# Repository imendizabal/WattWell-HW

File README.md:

# Aim of the project

The main goal of the project is to develop an open source inverter (Hardware and Software).  
This inverter should exist in different configurations: Monophasic (1-ph) and threephasic (3-ph). However, it is planned to be able to add a DC/DC converter for solar applications for example.

An important part of the project is to be able to work with different types of switching components (IGBT/MOSFET). Nowadays, we often see that inverters are replaced after 10 years but they keep working or some faulty inverters that are not easily repared because the design is not modular or easy to fix.

Then, the goal is to design an Open Source inverter that is modular to be easy to be fixed and flexible enough to have differents functionalities (batteries/PV/...)

The project will be divided into different "workpackages" or sub projects, on Hardware side we have:

1. Control board: development of the main control board able to get the measurements, generate PWM's, ... This board embeds the main mcu.
2. Driver board: interface between the control board and power switch (IGBT's/Mosfet's)
3. Power circuit: power circuit of the inverter (LCL filter, DC bus, ...)

on the firmware side (main mcu based on STM32G434):

1. Low level drivers
2. Basics functionalities (bootloader, debug uart, pll,...)
3. Advanced functionalities (power management, MPPT, state machine)

# Expected functionalities

- Being able (and allowed) to be connected to the European grid
- MPPT for solar panels (with DC/DC)
- Battery connection
- Communication capabilities (serial,...)
- Working in islanding mode (offgrid)

# 1. main control board:

The main control board will be able to measure:
1.  3AC voltages (max 400V) - ADC min 14bits
2.  2DC voltages (max 1500V) -ADC min 14bits
3.  4AC/DC current measurement - ADC min 14bits
4.  Temperature measurement

The main control board will have the following interface:
1.  2X UART(1X to RS485; 1X to USB)
2.  1xSPI
3.  2xI2C
4.  1xCAN
5.  6X PWM's
6.  6X DO's
7.  6X DI's
8.  6X AI'S (temp from IGBT/Mos)

Other functions:
1.  Debug LED
2.  RTC (supercap based)
3.  Additionnal ROM (TBD)
4.  Watchdog
5.  Power supply for IGBT's/Mosfets

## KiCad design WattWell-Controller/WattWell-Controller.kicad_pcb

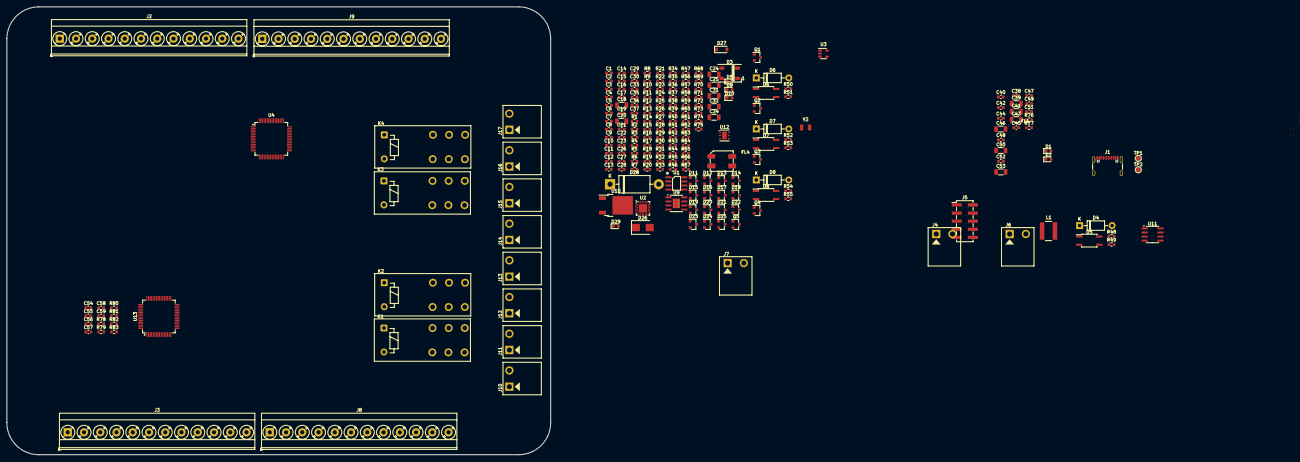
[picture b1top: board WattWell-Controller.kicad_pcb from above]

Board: 2 copper layers, 170.0 x 140.0 mm, 218 parts (0 on the bottom side), 168 nets, no tracks yet.

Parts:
C1, C3, C5, C7, C8, C10, C11, C12, C13, C14, C21, C22, C23, C27, C30, C33, C35, C36, C37, C49, C52: 100nF; C_0603_1608Metric
C2, C4, C6, C17, C19, C38, C40, C42, C44, C45, C47, C48, C51: 1uF; C_0603_1608Metric
C9: 10nF; C_0603_1608Metric
C15, C16: 9pF; C_0603_1608Metric
C18, C20, C39, C41, C43, C46, C50, C53: 22uF; C_1206_3216Metric
C24, C25: 10uF; C_1206_3216Metric
C26: 22nF; C_0603_1608Metric
C28: 47pF; C_0603_1608Metric
C29: 4.7nF; C_0603_1608Metric
C31, C32, C34: 47uF; C_1206_3216Metric
C54, C55, C56, C57, C58, C59: 1nF; C_0603_1608Metric
D1, D2: LED_Small; LED_0603_1608Metric
D3: WS2812B; LED_WS2812B_PLCC4_5.0x5.0mm_P3.2mm
D4, D6, D7, D8: 1N47xxA; D_DO-41_SOD81_P10.16mm_Horizontal
D5, D9, D10, D29: 150060RS55040; LED_0603_1608Metric
D11, D25: TVS_2-Channel-7V; SOT-23
D12: 824022; SOT-23
D13, D14, D15, D16, D17, D18, D19, D20, D21, D22, D23, D24: PESD3V3L2BT; SOT-23
D26: SMBJ30CA; D_SMB
D27: Zener_6V; D_SOD-123
D28: 1N5820; D_DO-201AD_P15.24mm_Horizontal
FL1, FL2, FL3: TCM0403M-350-2P-T210; Choke_TDK_TCM0403M-350-2P-T210
FL4: ACM7060-701-2PL-TL01; ChokeSMD_ACM7060
J1: USB_C_Receptacle_USB2.0; USB_C_Receptacle_GCT_USB4105-xx-A_16P_TopMnt_Horizontal
J2, J3, J8, J9: TerminalBlock_1x12; TerminalBlock_Phoenix_MKDS-3-12-5.08_1x12_P5.08mm_Horizontal
J4, J6, J7, J10, J11, J12, J13, J14, J15, J16, J17: 1x02; WURTH-691312510002
J5: Conn_ARM_JTAG_SWD_10; PinHeader_2x05_P2.54mm_Vertical_SMD
K1, K2, K3, K4: RZH3-1C4-D012; Relay_TE_RZH3-1C04-D012
L1: 10μH-5A; Inductor_Wurth_XHMI-6060
Q1, Q2, Q3, Q4: MMSS8050-H-TP; SOT-23
Q5: SI2347DS-T1-GE3; SOT-23
R1, R48, R49, R50, R51, R52, R53, R54, R55, R72, R73, R74: 120Ω; R_0603_1608Metric
R2, R3, R45, R46: 0; R_0603_1608Metric
R4, R5, R14, R15, R16, R17, R18, R19, R20, R21, R22, R23, R26, R27, R28, R29, R30, R31, R32, R33, R34, R35, R36, R37, R38, R39, R40, R41, R42, R47, R56, R57, R58, R59, R60, R61, R62, R63, R64, R65, R66, R67: 100; R_0603_1608Metric
R6: 22K1; R_0603_1608Metric
R7: 47K5; R_0603_1608Metric
R8, R78, R79, R80, R81, R82, R83: 1K; R_0603_1608Metric
R9, R10: 470Ω; R_0603_1608Metric
R11, R13, R43, R44, R76, R77: 10KΩ; R_0603_1608Metric
R12, R24, R25: 4K7; R_0603_1608Metric
R68: 12K; R_0603_1608Metric
R69: 49.9; R_0603_1608Metric
R70: 43KΩ; R_0603_1608Metric
R71: 8.2KΩ; R_0603_1608Metric
R75: 330; R_0603_1608Metric
TP1, TP2: TestPoint_1.5mm; TestPoint_Pad_D1.5mm
U1: SP3485EN; SOIC-8_3.9x4.9mm_P1.27mm
U2: CP2102N-A02-GQFN24; QFN-24-1EP_4x4mm_P0.5mm_EP2.6x2.6mm
U3: STWD100; SOT-23-5
U4, U13: LQFP-64_10x10mm_P0.5mm
U5, U6, U7, U8: LTV-356T; SO-4_4.4x3.6mm_P2.54mm
U9: TPS54331DR; SOIC-8-1EP_3.9x4.9mm_P1.27mm_EP2.29x3mm_ThermalVias
U10: BD33FC0FP-E2; TO-252-2
U11: ATA6560; SOIC-8_3.9x4.9mm_P1.27mm
U12: HDC2080; Texas_PWSON-N6
Y2: Crystal; Oscillator_SMD_ECS_2520MV-xxx-xx-4Pin_2.5x2.0mm

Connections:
+3V3: C1.1, C2.1, C8.1, C11.1, C12.1, C13.1, C14.1, C21.1, C22.1, C23.1, C34.1, C35.1, C36.1, C44.1, C46.1, C48.1, C50.1, D1.2 (K), D2.2 (K), J5.1 (VTref), R2.1, R8.1, R13.2, R24.2, R25.1, R45.1, R74.1, U2.5 (VIO), U2.6 (VDD), U2.7 (VREGIN), U3.5 (VCC), U4.16 (VDD), U4.29 (VDDA), U4.32 (VDD), U4.48 (VDD), U4.64 (VDD), U10.3 (Vout), U11.3 (VCC), U12.5 (VDD)
+5V: C17.1, C18.1, C19.1, C20.1, C31.1, C32.1, C33.1, C37.1, C38.1, C39.1, C40.1, C41.1, C42.1, C43.1, D3.4 (VDD), L1.2, R3.1, R70.1, R75.1, U10.1 (Vin)
+BATT: C10.1, U4.1 (VBAT)
/CAN_N: FL3.4, U11.6 (CANL)
/CAN_P: FL3.2, U11.7 (CANH)
/Dry Contact_1/DRY1_C: J11.2, K1.12
/Dry Contact_1/DRY1_O: J11.1, K1.14
/Dry Contact_1/DRY_CONT: J10.2, K1.11
/Dry Contact_1/DRY_V: D4.1 (K), J10.1, K1.A2, U5.4
/Dry Contact_2/DRY1_C: J12.2, K2.12
/Dry Contact_2/DRY1_O: J12.1, K2.14
/Dry Contact_2/DRY_CONT: J13.2, K2.11
/Dry Contact_2/DRY_V: D6.1 (K), J13.1, K2.A2, U6.4
/Dry Contact_3/DRY1_C: J15.2, K3.12
/Dry Contact_3/DRY1_O: J15.1, K3.14
/Dry Contact_3/DRY_CONT: J14.2, K3.11
/Dry Contact_3/DRY_V: D7.1 (K), J14.1, K3.A2, U7.4
/Dry Contact_4/DRY1_C: J17.2, K4.12
/Dry Contact_4/DRY1_O: J17.1, K4.14
/Dry Contact_4/DRY_CONT: J16.2, K4.11
/Dry Contact_4/DRY_V: D8.1 (K), J16.1, K4.A2, U8.4
/EXT_CAN_N: D11.2, FL3.3, J6.2
/EXT_CAN_P: D11.1, FL3.1, J6.1
/IN_AN1: D24.3, J8.1
/IN_AN2: D24.1, J8.3
/IN_AN3: D19.1, D23.3, J2.12 (Pin_8), J8.5, R33.1
/IN_AN4: D23.1, J8.7 (Pin_10)
/IN_AN5: D22.3, J8.9 (Pin_12)
/IN_AN6: D22.1, J8.12 (Pin_8)
/IN_DIG1: D21.3, J2.1, R28.1
/IN_DIG2: D21.1, J2.3, R29.1
/IN_DIG3: D20.3, J2.5, R30.1
/IN_DIG4: D20.1, J2.7 (Pin_10), R31.1
/IN_DIG5: D19.3, J2.9 (Pin_12), R32.1
/JTCK: J5.4 (SWDCLK/TCK), R58.1
/JTDI: J5.8 (NC/TDI), R59.1
/JTDO: J5.6 (SWO/TDO), R66.2, R67.2
/JTMS: J5.2 (SWDIO/TMS), R57.1
/MCU/IN_AN5: R82.1, R83.1
/MCU/LED1: R72.1, U4.55 (PD2)
/MCU/LED2: R73.1, U4.30 (PB10)
/MCU/MCU_RST: C9.2, R12.2, R13.1, U4.7 (NRST)
/MCU/RS485: U1.2 (~RE), U1.3 (DE), U2.12 (RS485/IO2)
/MCU/RX0_3V3: R4.1, U2.21 (TXD)
/MCU/SCL: R25.2, U12.6 (SCL)
/MCU/SDA: R24.1, U12.1 (SDA)
/MCU/TX0_3V3: R5.1, U2.20 (RXD)
/MCU/VCAP2: C51.1, C52.1, U13.30 (VCAP2)
/MCU/VCAP3: C47.1, C49.1, U13.55 (VCAP3)
/MCU/VCAP4: C45.1, U13.26 (VCAP4)
/OUT_DIG1: D18.3, J3.1, R14.1
/OUT_DIG2: D18.1, J3.3, R15.1
/OUT_DIG3: D17.3, J3.5, R22.1
/OUT_DIG4: D17.1, J3.7 (Pin_10), R23.1
/OUT_DIG5: D16.3, J3.9 (Pin_12), R26.1
/OUT_DIG6: D16.1, J3.12 (Pin_8), R27.1
/OUT_PWM1: D15.3, J9.1, R34.1
/OUT_PWM2: D15.1, J9.3, R35.1
/OUT_PWM3: D14.3, J9.5, R36.1
/OUT_PWM4: D14.1, J9.7 (Pin_10), R37.1
/OUT_PWM5: D13.3, J9.9 (Pin_12), R38.1
/OUT_PWM6: D13.1, J9.12 (Pin_8), R56.1
/RS485_EXT_N: D25.1, FL2.3, J4.2
/RS485_EXT_P: D25.2, FL2.1, J4.1
/RS485_N: FL2.4, R1.2, U1.7 (B)
/RS485_P: FL2.2, R1.1, U1.6 (A)
/USB_D_N: FL1.4, U2.4 (D-)
/USB_D_P: FL1.2, U2.3 (D+)
/USB_IN_N: D12.1 (IO1), FL1.3, J1.A6 (D+), J1.B6 (D+)
/USB_IN_P: D12.3 (IO2), FL1.1, J1.A7 (D-), J1.B7 (D-)
GND: C1.2, C2.2, C3.2, C4.2, C5.2, C6.2, C7.2, C8.2, C9.1, C10.2, C11.2, C12.2, C13.2, C14.2, C15.2, C16.2, C17.2, C18.2, C19.2, C20.2, C21.2, C22.2, C23.2, C26.2, C28.2, C31.2, C32.2, C33.2, C34.2, C35.2, C36.2, C37.2, C38.2, C39.2, C40.2, C41.2, C42.2, C43.2, C44.2, C45.2, C46.2, C47.2, C48.2, C49.2, C50.2, C51.2, C52.2, C53.2, C54.2, C55.2, C56.2, C57.2, C58.2, C59.2, D3.2 (GND), D5.2 (K), D9.2 (K), D10.2 (K), D11.3, D12.2 (GND), D13.2, D14.2, D15.2, D16.2, D17.2, D18.2, D19.2, D20.2, D21.2, D22.2, D23.2, D24.2, D25.3, D28.2 (A), D29.2 (K), J1.A1 (GND), J1.A12 (GND), J1.B1 (GND), J1.B12 (GND), J1.S1 (SHIELD), J2.2, J2.4, J2.6, J2.8 (Pin_11), J2.10 (Pin_13), J2.11 (Pin_7), J3.2, J3.4, J3.6, J3.8 (Pin_11), J3.10 (Pin_13), J3.11 (Pin_7), J5.3 (GND), J5.5 (GND), J5.9 (GNDDetect), J8.2, J8.4, J8.6, J8.8 (Pin_11), J8.10 (Pin_13), J8.11 (Pin_7), J9.2, J9.4, J9.6, J9.8 (Pin_11), J9.10 (Pin_13), J9.11 (Pin_7), R7.2, R11.2, R43.2, R44.2, R46.2, R69.2, R71.2, R76.2, R77.2, U1.5 (GND), U2.2 (GND), U2.25 (GND), U3.2 (GND), U4.15 (VSS), U4.27 (VSSA), U4.31 (VSS), U4.47 (VSS), U4.63 (VSS), U5.2, U6.2, U7.2, U8.2, U9.7 (GND), U9.9 (PAD), U10.2 (GND), U11.2 (GND), U12.2 (GND), U13.1 (IN8N), U13.2 (IN8P), U13.3 (IN7N), U13.4 (IN7P), U13.5 (IN6N), U13.7 (IN5N), U13.9 (IN4N), U13.11 (IN3N), U13.13 (IN2N), U13.15 (IN1N), U13.20 (AVSS), U13.23 (AVSS), U13.27 (REFN), U13.32 (AVSS), U13.33 (DGND), U13.49 (DGND), U13.51 (DGND), U13.53 (AVSS1), U13.57 (AVSS), U13.58 (AVSS)
GND1: Q1.2 (E), Q2.2 (E), Q3.2 (E), Q4.2 (E)
unnamed: C24.2, C25.2, C27.2, FL4.3
unnamed: C29.2, R69.1
unnamed: D1.1 (A), R9.2
unnamed: D2.1 (A), R10.2
unnamed: D4.2 (A), K1.A1, Q1.3 (C)
unnamed: D5.1 (A), R72.2
unnamed: D6.2 (A), K2.A1, Q2.3 (C)
unnamed: D7.2 (A), K3.A1, Q3.3 (C)
unnamed: D8.2 (A), K4.A1, Q4.3 (C)
unnamed: D9.1 (A), R73.2
unnamed: D10.1 (A), R74.2
unnamed: D26.1 (A1), J7.2, R68.1
unnamed: D26.2 (A2), J7.1, Q5.3 (D)
unnamed: D27.2 (A), Q5.1 (G), R68.2
unnamed: D27.1 (K), Q5.2 (S)
unnamed: C30.2, D28.1 (K), L1.1, U9.8 (PH)
unnamed: D29.1 (A), R75.2
unnamed: Q1.1 (B), R48.1
unnamed: Q2.1 (B), R50.1
unnamed: Q3.1 (B), R52.1
unnamed: Q4.1 (B), R54.1
unnamed: R48.2, U5.3
unnamed: R49.1, U5.1
unnamed: R50.2, U6.3
unnamed: R51.1, U6.1
unnamed: R52.2, U7.3
unnamed: R53.1, U7.1
unnamed: R54.2, U8.3
unnamed: R55.1, U8.1
unnamed: R5.2, U1.4 (DI)
unnamed: R4.2, U1.1 (RO)
unnamed: C7.1, R2.2, R3.2, U1.8 (VCC)
unnamed: R9.1, U2.13 (RXT/IO1)
unnamed: R10.1, U2.14 (TXT/IO0)
unnamed: R6.2, R7.1, U2.8 (VBUS)
unnamed: R8.2, U2.9 (~RST)
unnamed: R11.1, U2.15 (~SUSPEND)
unnamed: R12.1, U3.1 (~WDO)
unnamed: C16.1, U4.3 (OSC32_IN), Y2.1
unnamed: C15.1, U4.4 (OSC32_OUT), Y2.2
unnamed: R34.2, U4.12 (PA0)
unnamed: R35.2, U4.13 (PA1)
unnamed: R36.2, U4.14 (PA2)
unnamed: R37.2, U4.17 (PA3)
unnamed: R38.2, U4.18 (PA4)
unnamed: R39.2, U4.19 (PA5)
unnamed: R40.2, U4.20 (PA6)
unnamed: R41.2, U4.21 (PA7)
unnamed: R42.2, U4.42 (PA8)
unnamed: R47.2, U4.43 (PA9)
unnamed: R56.2, U4.46 (PA12)
unnamed: R57.2, U4.49 (PA13)
unnamed: R58.2, U4.50 (PA14)
unnamed: R59.2, U4.51 (PA15)
unnamed: R64.1, U4.24 (PB0)
unnamed: R65.1, U4.25 (PB1)
unnamed: R66.1, U4.56 (PB3)
unnamed: R67.1, U4.57 (PB4)
unnamed: R60.1, U4.33 (PB11)
unnamed: R61.1, U4.34 (PB12)
unnamed: R62.1, U4.35 (PB13)
unnamed: R63.1, U4.36 (PB14)
unnamed: R14.2, U4.8 (PC0)
unnamed: R15.2, U4.9 (PC1)
unnamed: R22.2, U4.10 (PC2)
unnamed: R23.2, U4.11 (PC3)
unnamed: R26.2, U4.22 (PC4)
unnamed: R27.2, U4.23 (PC5)
unnamed: R28.2, U4.38 (PC6)
unnamed: R29.2, U4.39 (PC7)
unnamed: R30.2, U4.40 (PC8)
unnamed: R31.2, U4.41 (PC9)
unnamed: R32.2, U4.52 (PC10)
unnamed: R33.2, U4.53 (PC11)
unnamed: C30.1, U9.1 (BOOT)
unnamed: C28.1, C29.1, U9.6 (COMP)
unnamed: C26.1, U9.4 (SS)
unnamed: C24.1, C25.1, C27.1, FL4.4, U9.2 (VIN)
unnamed: R70.2, R71.1, U9.5 (VSENSE)
unnamed: R45.2, R46.1, U12.3 (ADDR)
unnamed: U13.48 (DVDD), U13.50 (DVDD), U13.54 (AVDD1)
unnamed: U13.19 (AVDD), U13.21 (AVDD), U13.22 (AVDD), U13.56 (AVDD), U13.59 (AVDD)
unnamed: R77.1, U13.42 (GPIO1)
unnamed: R76.1, U13.44 (GPIO2)
unnamed: R44.1, U13.45 (GPIO3)
unnamed: R43.1, U13.46 (GPIO4)
unnamed: C54.1, R78.2, U13.16 (IN1P)
unnamed: C55.1, R79.2, U13.14 (IN2P)
unnamed: C56.1, R80.2, U13.12 (IN3P)
unnamed: C57.1, R81.2, U13.10 (IN4P)
unnamed: C58.1, R82.2, U13.8 (IN5P)
unnamed: C59.1, R83.2, U13.6 (IN6P)
unnamed: TP1.1, U13.18 (TESTN)
unnamed: TP2.1, U13.17 (TESTP)
unnamed: C53.1, U13.28 (VCAP1)
VBUS: C3.1, C4.1, C5.1, C6.1, J1.A4 (VBUS), J1.A9 (VBUS), J1.B4 (VBUS), J1.B9 (VBUS), R6.1

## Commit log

2022-09-27 Kicad schematic started: added the first filtering components
2022-12-08 Added libraries
    Schematic: Added USB / UART transceiver
2022-12-11 Added Communications sheet - Added USB / UART transceiver - Added UART / RS485
2022-12-20 Added temperature sensor and LED
2023-01-02 Added power supply stages: 5V, 3.3V
2023-01-03 Added an ADC
2023-03-21 Migrated Kicad symbol libraries to the last version (extension .kicad_sym) Adding microcontroller STM32G474RET6
2023-03-23 Added microcontroller Added watchdog
2023-04-01 - Added Oscillators symbol library - Schematic continued: added input and output nets. Power 3.3V connected to the MCU. Added decoupling capacitors
2023-04-07 Added 24 pin connectors
2023-04-08 Added CAN transceiver
2023-04-29 Specified the README file
2023-05-26 Assigned input and outputs to the MCU
2023-06-07 Added relay circuits Changed the schematic size from A3 to A2
2023-06-08 Added graphic rectangles to organize the schematics Added connectors Resized the sheet from A2 to A3 Added Dry contact in a hierarchical sheet
2023-06-17 Schematic continued: Added ADCs, dry contacts
2023-06-25 Schematic continued. TODO: add protections
2023-06-28 Added LEDS. Protections on going
2023-06-29 Protections in I/O added
2023-06-30 Added filters Added JTAG connector
2023-09-16 Added crystal footprint
2023-09-20 Added choke footprint TCM0403M-350-2P-T210
2023-11-04 Added the ADC ADS131E06 to the schematic libraries and to the project
2023-12-18 Converting the design into a hierarchical one
2024-01-08 Continued the organization of a hierarchical schematic
2024-05-24 Added footprints of some components
    Started to add footprints to shape the PCB
2024-05-24 Added more footprints
2024-05-26 Added more footprints
    Schematic organized, less subsheets. More clarity
2024-05-26 Schematic continued
    Ongoing: MCU dimensioning. Evaluating the need of using a bigger package to access to more functionalities without multiplexing the MCU pins
2024-08-11 Added connectors, board outline defined and started placement
2024-08-17 Added RC filters to the ADC (Values to be set) ADC connected to GND and Power Connectors added for the relays outputs
